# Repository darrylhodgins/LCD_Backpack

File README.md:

I2C-Enabled LCD Backpack
========================

Loosely based on [
*Serial Enabled LCD Backpack (LCD-00258)*](https://www.sparkfun.com/products/258)

This backpack allows you to control a parallel based LCD over an I2C serial interface.
It is compatible with 16x2 LCDs and 20x4 LCDs.

Repository Contents
-------------------

* **/Firmware** - Any firmware that the part ships with, 
* **/Hardware** - All Eagle design files (.brd, .sch, .STL)

License Information
-------------------
The hardware is released under [Creative Commons ShareAlike 4.0 International](https://creativecommons.org/licenses/by-sa/4.0/).

Distributed as-is; no warranty is given.

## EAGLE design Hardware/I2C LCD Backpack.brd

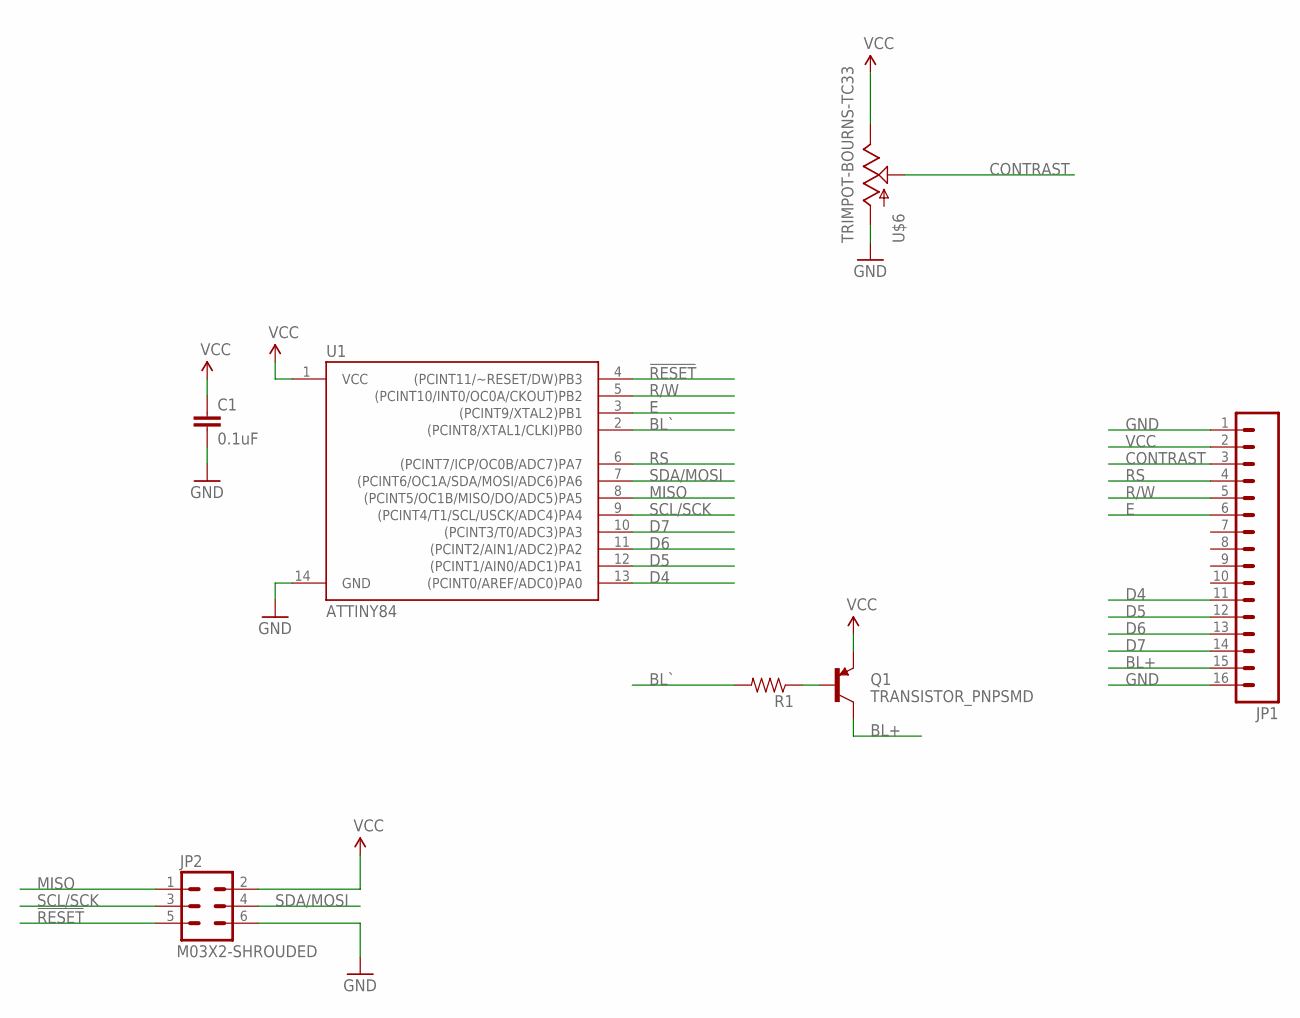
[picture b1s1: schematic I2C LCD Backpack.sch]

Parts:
C1: 0.1uF; 0603-CAP
JP1: M16PTH; 1X16
JP2: M03X2-SHROUDED; 2X3-SHROUDED-B
Q1: TRANSISTOR_PNPSMD; SOT23-3
R1: RESISTOR0603-RES; 0603-RES
U1: ATTINY84; SO14
U$6: TRIMPOT-BOURNS-TC33

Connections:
!RESET: JP2.5, U1.4 ((PCINT11/~RESET/DW)PB3)
BL+: JP1.15, Q1.3 (C)
BL`: R1.2, U1.2 ((PCINT8/XTAL1/CLKI)PB0)
CONTRAST: JP1.3, U$6.2 (S)
D4: JP1.11, U1.13 ((PCINT0/AREF/ADC0)PA0)
D5: JP1.12, U1.12 ((PCINT1/AIN0/ADC1)PA1)
D6: JP1.13, U1.11 ((PCINT2/AIN1/ADC2)PA2)
D7: JP1.14, U1.10 ((PCINT3/T0/ADC3)PA3)
E: JP1.6, U1.3 ((PCINT9/XTAL2)PB1)
GND: C1.2, JP1.1, JP1.16, JP2.6, U1.14 (GND), U$6.1 (A)
MISO: JP2.1, U1.8 ((PCINT5/OC1B/MISO/DO/ADC5)PA5)
unnamed: Q1.1 (B), R1.1
R/W: JP1.5, U1.5 ((PCINT10/INT0/OC0A/CKOUT)PB2)
RS: JP1.4, U1.6 ((PCINT7/ICP/OC0B/ADC7)PA7)
SCL/SCK: JP2.3, U1.9 ((PCINT4/T1/SCL/USCK/ADC4)PA4)
SDA/MOSI: JP2.4, U1.7 ((PCINT6/OC1A/SDA/MOSI/ADC6)PA6)
VCC: C1.1, JP1.2, JP2.2, Q1.2 (E), U1.1 (VCC), U$6.3 (E)

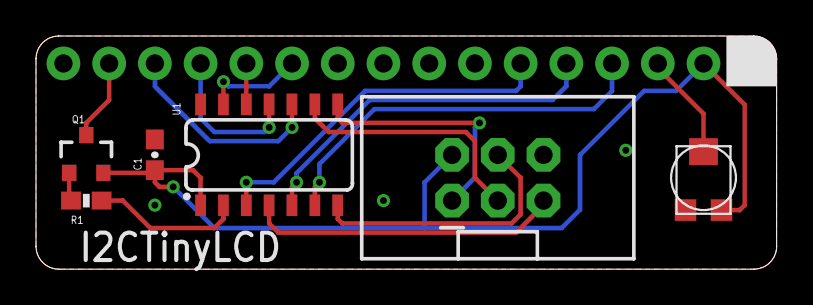
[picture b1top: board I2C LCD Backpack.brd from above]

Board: 2 copper layers, 41.1 x 13.0 mm, 7 parts (1 on the bottom side), 17 nets.

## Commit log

2016-06-17 Replaced most parts with other parts. The only thing that really remains from the original Sparkfun design is the shape.

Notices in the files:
parts and their libraries:
SparkFun-DigitalIC: Licensing: Creative Commons ShareAlike 4.0 International - https://creativecommons.org/licenses/by-sa/4.0
